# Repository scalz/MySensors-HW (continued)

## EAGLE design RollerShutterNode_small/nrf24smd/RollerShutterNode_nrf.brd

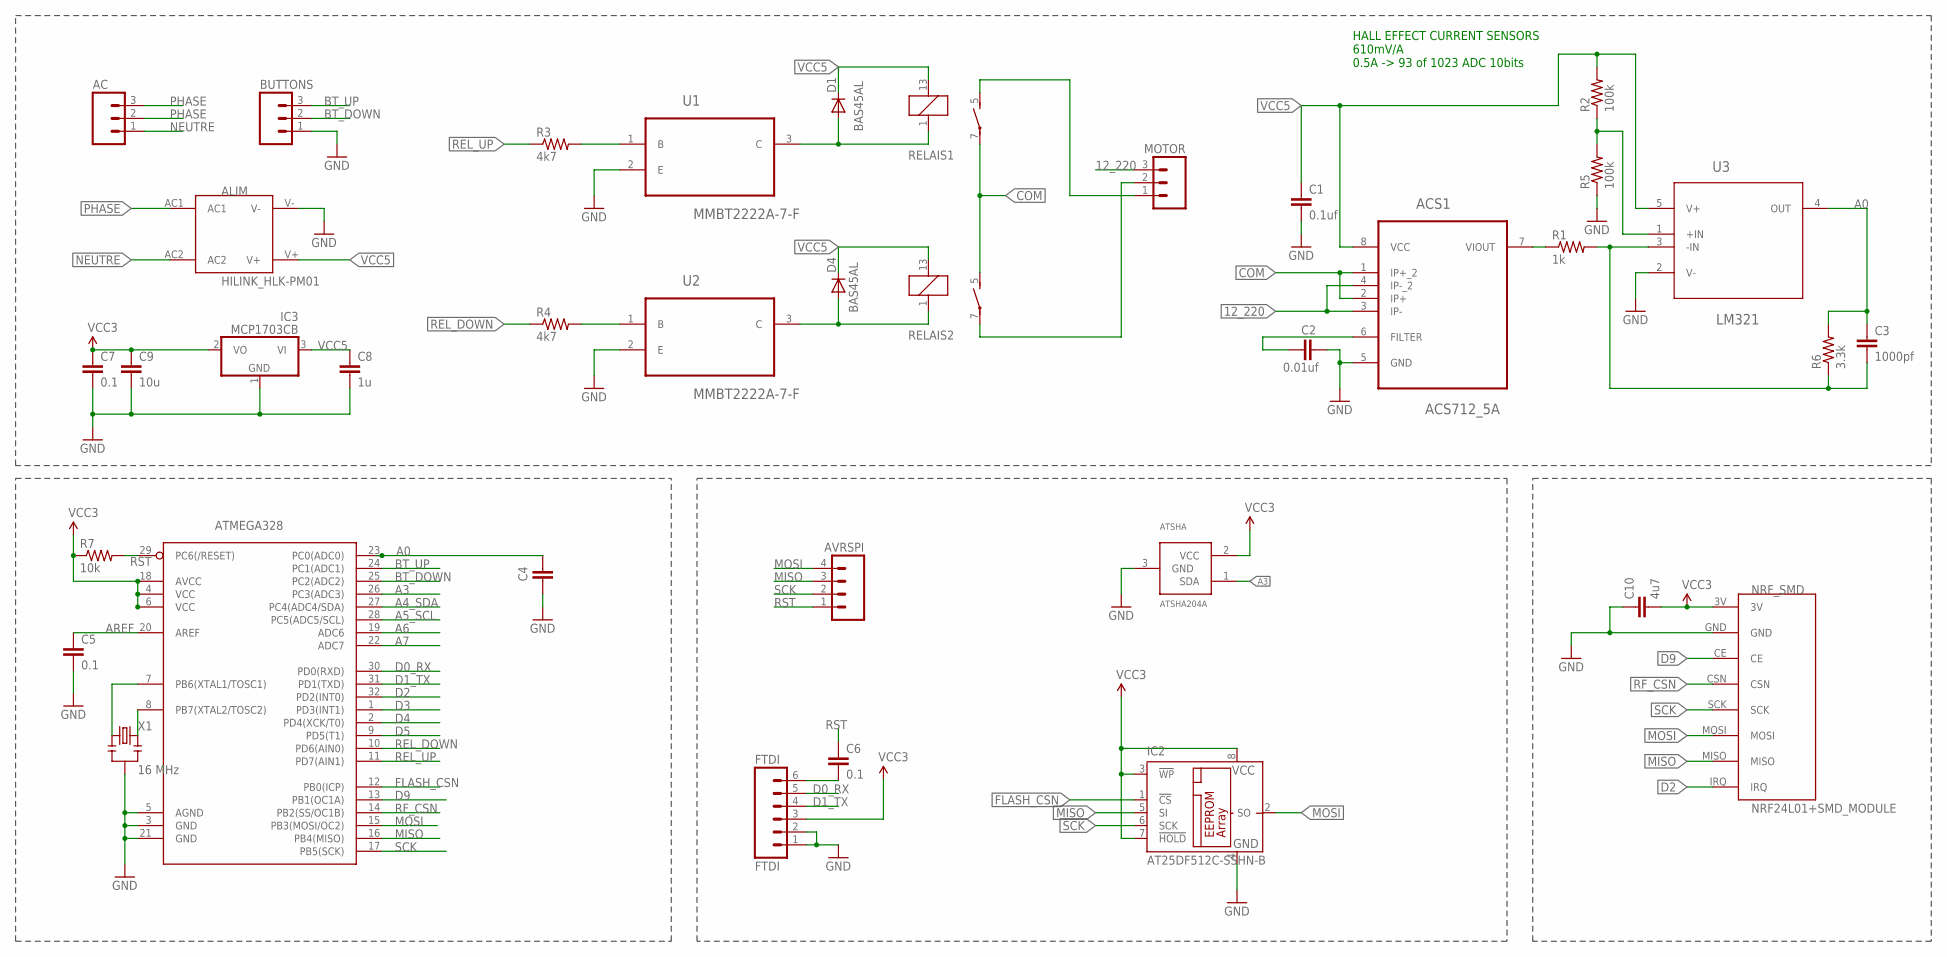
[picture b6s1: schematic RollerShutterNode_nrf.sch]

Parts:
AC: M03SCREW; SCREWTERMINAL-3.5MM-3
ACS1: ACS712_5A; SOIC127P600X175-8N
ALIM: HILINK_HLK-PM01
ATMEGA328: ATMega-328; TQFP32-08
ATSHA: ATSHA204A; SOT23
AVRSPI: M04PTH; 1X04
BUTTONS: M03SCREW; SCREWTERMINAL-3.5MM-3
C1: 0.1uf; 0805
C2: 0.01uf; 0805
C3: 1000pf; 0805
C4: CAP0805; 0805
C5, C6, C7: 0.1; 0805
C8: 1u; 0805
C9: 10u; 0805-CAP
C10: 4u7; 0805
D1, D4: BAS45AL; SOD80C
FTDI: FTDI; 1X06
IC2: AT25DF512C-SSHN-B; SO-08
IC3: MCP1703CB; SOT23
MOTOR: M03SCREW; SCREWTERMINAL-3.5MM-3
NRF_SMD: NRF24L01+SMD_MODULE
R1: 1k; 0805
R2, R5: 100k; 0805
R3, R4: 4k7; 0805
R6: 3.3k; 0805
R7: 10k; 0805
RELAIS1, RELAIS2: Relais G6D; G6D
U1, U2: MMBT2222A-7-F; SOT103P240X110-3N
U3: LM321; SOT95P285X120-5N
X1: 16 MHz; RESONATOR-SMD

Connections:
12_220: ACS1.3 (IP-), ACS1.4 (IP-_2), MOTOR.3
A0: ATMEGA328.23 (PC0(ADC0)), C3.1, C4.2, R6.2, U3.4 (OUT)
A3: ATMEGA328.26 (PC3(ADC3)), ATSHA.1 (SDA)
A4_SDA: ATMEGA328.27 (PC4(ADC4/SDA))
A5_SCL: ATMEGA328.28 (PC5(ADC5/SCL))
A6: ATMEGA328.19 (ADC6)
A7: ATMEGA328.22 (ADC7)
AREF: ATMEGA328.20 (AREF), C5.1
BT_DOWN: ATMEGA328.25 (PC2(ADC2)), BUTTONS.2
BT_UP: ATMEGA328.24 (PC1(ADC1)), BUTTONS.3
COM: ACS1.1 (IP+_2), ACS1.2 (IP+), RELAIS1.7, RELAIS2.5 (S)
D0_RX: ATMEGA328.30 (PD0(RXD)), FTDI.5
D1_TX: ATMEGA328.31 (PD1(TXD)), FTDI.4
D2: ATMEGA328.32 (PD2(INT0)), NRF_SMD.IRQ
D3: ATMEGA328.1 (PD3(INT1))
D4: ATMEGA328.2 (PD4(XCK/T0))
D5: ATMEGA328.9 (PD5(T1))
D9: ATMEGA328.13 (PB1(OC1A)), NRF_SMD.CE
FLASH_CSN: ATMEGA328.12 (PB0(ICP)), IC2.1 (!CS)
GND: ACS1.5 (GND), ALIM.V-, ATMEGA328.3 (GND), ATMEGA328.5 (AGND), ATMEGA328.21 (GND), ATSHA.3 (GND), BUTTONS.1, C1.2, C2.2, C4.1, C5.2, C7.2, C8.2, C9.2, C10.1, FTDI.1, FTDI.2, IC2.4 (GND), IC3.1 (GND), NRF_SMD.GND, R5.1, U1.2 (E), U2.2 (E), U3.2 (V-), X1.2
MISO: ATMEGA328.16 (PB4(MISO)), AVRSPI.3, IC2.5 (SI), NRF_SMD.MISO
MOSI: ATMEGA328.15 (PB3(MOSI/OC2)), AVRSPI.4, IC2.2 (SO), NRF_SMD.MOSI
unnamed: ACS1.6 (FILTER), C2.1
unnamed: ACS1.7 (VIOUT), R1.1
unnamed: R3.2, U1.1 (B)
unnamed: R4.2, U2.1 (B)
unnamed: D4.A, RELAIS2.1, U2.3 (C)
unnamed: MOTOR.1, RELAIS1.5 (S)
unnamed: D1.A, RELAIS1.1, U1.3 (C)
unnamed: MOTOR.2, RELAIS2.7
unnamed: C3.2, R1.2, R6.1, U3.3 (-IN)
unnamed: R2.1, R5.2, U3.1 (+IN)
unnamed: ATMEGA328.7 (PB6(XTAL1/TOSC1)), X1.1
unnamed: C6.2, FTDI.6
unnamed: ATMEGA328.8 (PB7(XTAL2/TOSC2)), X1.3
NEUTRE: AC.1, ALIM.AC2
PHASE: AC.2, AC.3, ALIM.AC1
REL_DOWN: ATMEGA328.10 (PD6(AIN0)), R4.1
REL_UP: ATMEGA328.11 (PD7(AIN1)), R3.1
RF_CSN: ATMEGA328.14 (PB2(SS/OC1B)), NRF_SMD.CSN
RST: ATMEGA328.29 (PC6(/RESET)), AVRSPI.1, C6.1, R7.2
SCK: ATMEGA328.17 (PB5(SCK)), AVRSPI.2, IC2.6 (SCK), NRF_SMD.SCK
VCC: ATMEGA328.4 (VCC), ATMEGA328.6 (VCC), ATMEGA328.18 (AVCC), ATSHA.2 (VCC), C7.1, C9.1, C10.2, FTDI.3, IC2.3 (!WP), IC2.7 (!HOLD), IC2.8 (VCC), IC3.2 (VO), NRF_SMD.3V, R7.1
VCC5: ACS1.8 (VCC), ALIM.V+, C1.1, C8.1, D1.C, D4.C, IC3.3 (VI), R2.2, RELAIS1.13 (2), RELAIS2.13 (2), U3.5 (V+)

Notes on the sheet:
HALL EFFECT CURRENT SENSORS 610mV/A 0.5A -> 93 of 1023 ADC 10bits

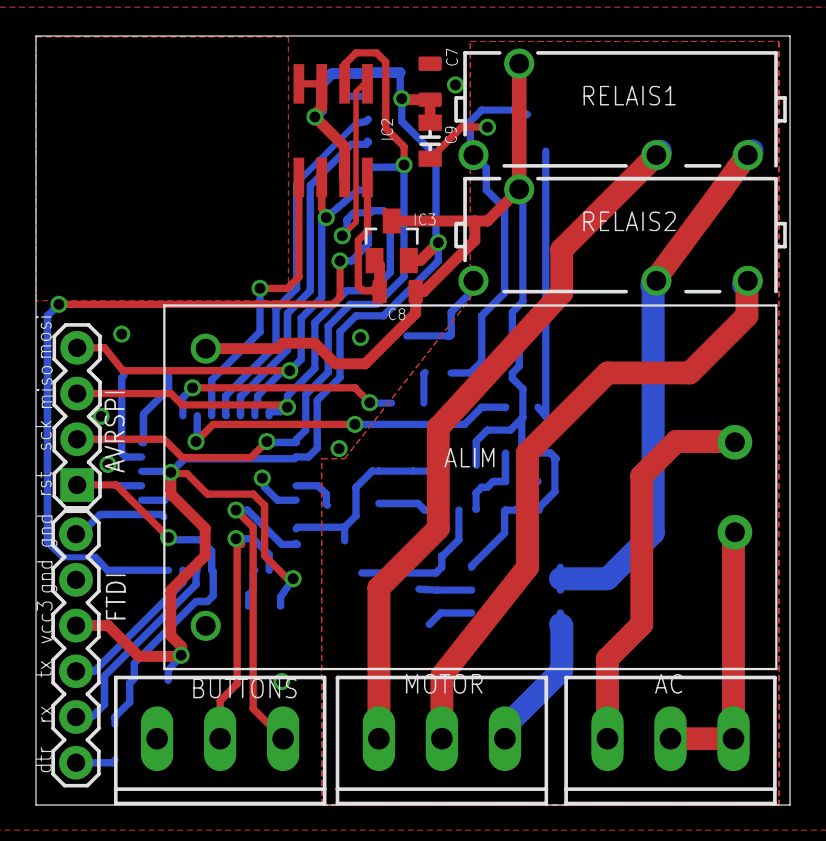
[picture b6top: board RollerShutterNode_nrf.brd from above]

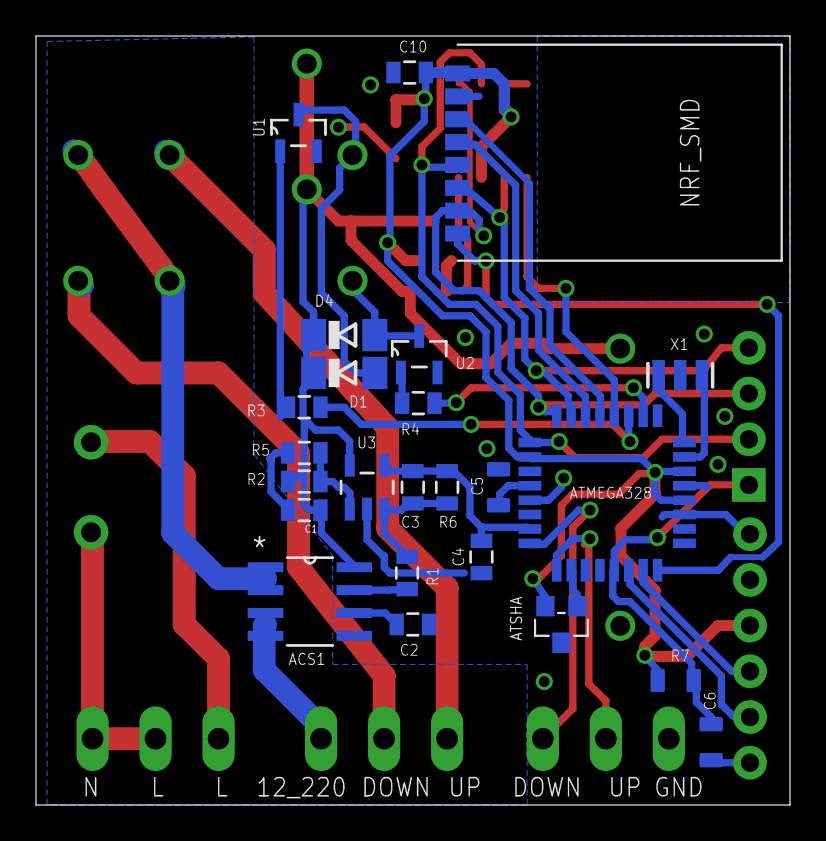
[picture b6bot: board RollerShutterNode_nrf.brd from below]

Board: 2 copper layers, 41.9 x 42.7 mm, 37 parts (24 on the bottom side), 37 nets.
